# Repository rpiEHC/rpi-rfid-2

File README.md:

# RPI RFID

The goal of RPI RFID is to design, build and test an RPI id card (HID Proxcard II) reader.

## Getting Started

After cloning the repo, execute the following commands to get all the libraries we use for the project.

`git submodule init` 
`git submodule update`

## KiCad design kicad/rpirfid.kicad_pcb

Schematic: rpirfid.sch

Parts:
1K1: R; R_1210
ACT1: LED; LED-1206
C1, C2, C3: 1uF; C_1206
C4, C9, C10, C11: 100nF; C_1206
C5, C6, C7: 10nF; C_1206
C8, C12: 1nF; C_1206
Crystal1: 32.768kHz; Crystal_Round_Horizontal_2mm
D1, D2, D3, D4: LED; LED-1206
IC1: 4050; HEX4045
P1: USB_A
P2: POWER; AK300-2
P3: AVR_PRG_SPI; AK300-2
P4: BATTERY INPUT; AK300-2
R1, R2: 22; R_1206
R3: 10k; R_1206
R4, R7: 470; R_1206
R5, R6: 1k; R_1206
R8: R; R_1206
SW1: SW_PUSH; SW_PUSH_SMALL
U1: ATMEGA32U4-A; TQFP_44
U2: SD_Card_Revised; DIP-8_W7.62mm
U3: EM4095; SOIC-16_3.9x9.9mm_Pitch1.27mm
U4: LM7805; PINHEAD1-3
U5: LD1117S33CTR; PINHEAD1-3
U6: ds1307; DIP-8_W7.62mm
X1: CRYSTAL_SMD; Crystal_Round_Vertical_2mm

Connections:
/3.3V: U2.4, U5.2
/ANT: C8.2, R8.1
/AVR_MISO: P3.1, U1.11, U2.7
/AVR_MOSI: IC1.5, U1.10
/AVR_RESET: R3.1, SW1.2, U1.13
/AVR_SCLK: IC1.3, IC1.9, U1.9
/CDV: C8.1, C12.2, U3.8
/CardDetect: U1.31
/CardSelect: IC1.7, U1.12
/RES_LED: R7.2, U1.29
/RFID_CLK: U1.20, U3.2
/RFID_DATA: U1.21, U3.13
/RFID_EN: U1.25, U3.14
/RFID_MOD: U1.37, U3.12
/RXLED: D1.1, U1.8
/SCL: U1.18, U6.6
/SDA: U1.19, U6.5
/TXLED: D3.1, U1.22
/USB_VBUS: P1.1, U1.2, U1.7
/VBATT: P4.2, U4.1 (VI), U5.3
GND: C1.2, C2.2, C3.1, C5.1, C6.1, C7.1, C12.1, D2.1, D4.1, IC1.11, IC1.14, P1.4, P2.2, P4.1, SW1.1, U1.5, U1.15, U1.23, U1.35, U1.43, U2.6, U3.1, U3.5, U4.2 (GND), U5.1, U6.4
unnamed: 1K1.1, IC1.6, U2.2
unnamed: 1K1.2, ACT1.1
unnamed: ACT1.2, IC1.10
unnamed: C2.1, U1.6
unnamed: C3.2, U1.42
unnamed: C4.1, U3.9
unnamed: C4.2, U3.10
unnamed: C5.2, U3.15
unnamed: C6.2, U3.11
unnamed: C7.2, U3.16
unnamed: C9.1, C10.1, C11.1, U3.6
unnamed: C9.2, C10.2, C11.2
unnamed: Crystal1.1, U6.1
unnamed: Crystal1.2, U6.2
unnamed: D1.2, R5.2
unnamed: D2.2, R4.1
unnamed: D3.2, R6.2
unnamed: D4.2, R7.1
unnamed: IC1.2, U2.5
unnamed: IC1.4, U2.3
unnamed: P1.2, R2.2
unnamed: P1.3, R1.2
unnamed: R1.1, U1.4
unnamed: R2.1, U1.3
unnamed: R8.2, U3.3
unnamed: U1.16, X1.2
unnamed: U1.17, X1.1
VCC: C1.1, IC1.1, P2.1, P3.2, R3.2, R4.2, R5.1, R6.1, U1.14, U1.24, U1.34, U1.44, U3.7, U6.8
VSS: IC1.8

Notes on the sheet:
Real Time Clock
AVR Programmer
Transceiver/Antenna Circuit
USB INPUT
POWER LED
Response LED
TX & RX LED
BATTERY POWER
5V REG
3V REG

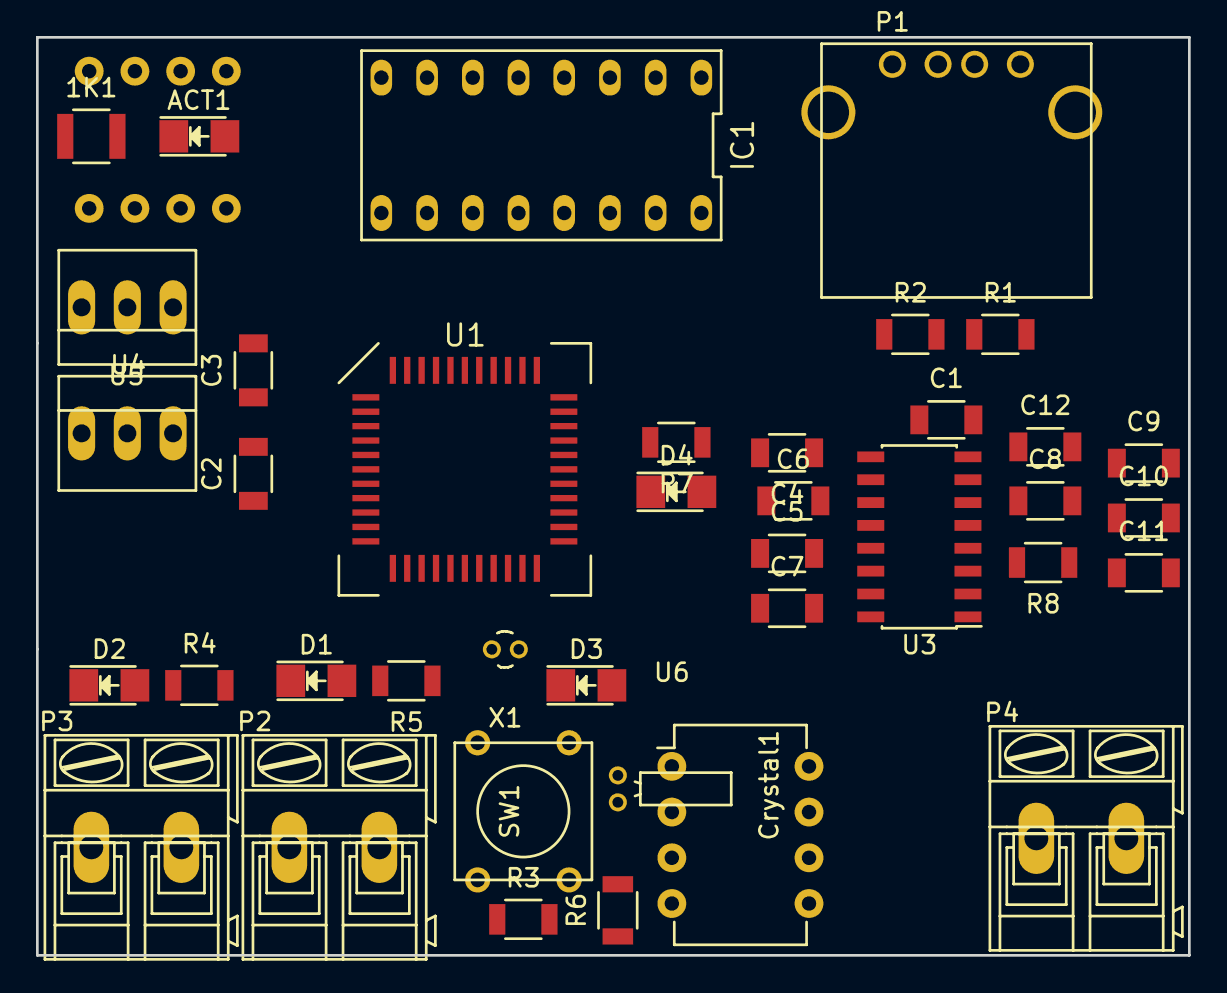
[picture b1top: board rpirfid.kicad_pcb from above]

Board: 2 copper layers, 64.0 x 51.0 mm, 40 parts (1 on the bottom side), 48 nets, no tracks yet.

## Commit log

2015-09-05 initial- old eagle files
2015-09-29 added legacy files
2015-09-29 removed not "up to date" legacy eagle files
2015-10-16 Datasheets
    Datasheets for ICs in the legacy circuit
2015-10-16 More PDFs
    PDFs of the legacy board and schematic
2015-10-16 Even more PDFs and schematics & boards
    Fixed the pdf of the legacy circuit schematic
    Added reference files to the Adafruit microsdcard breakoutboard
2015-10-20 Fixed sd card eagle reference files
    Old files had some weird html stuff in it, replaced with files without
2015-10-21 initial board w/ microcontroller, programmer and usb port (in schematic)
2015-10-21 added microcontroller to datasheets directory
2015-10-30 Custom Library
    Added Part
2015-10-30 Added new component library
2015-10-30 Updated Leglamp library
    Added SD Card to library
2015-10-30 Added real time clock
2015-10-30 Revert "Added real time clock"
    This reverts commit 6b6fc6739ad60bcd637f11be7c206d4bd97eeb06.
2015-11-06 SD_Card added
2015-11-14 SD Card
    Added a Kicad circuit for the SD Card and added another schematic for
    the SD Card in the leglamp library
2015-11-14 Real time clock stuff
2015-11-20 antenna pcb
2015-11-20 added voltage regulator and antenna to schematic
2015-11-20 SD Card
    Added SD Card to the SD Card folder
2015-11-20 Removed the SD_Card circuit from the SD_Card folder
2015-11-20 em4095 module
2015-11-20 Trying to add in SD Card & SD Card Datasheet
2015-11-21 SD Card added to the main file
2015-11-21 Slight update with GND
2015-11-21 Fixed Labels and Connected SD Card to Microcontroller
2015-11-21 Fully connected SD Card and labels
2015-11-21 PCB was started
2015-12-03 created last footprint schematics
2015-12-04 added hex buffer
2015-12-05 corrected name of hex buffer
2015-12-05 SO16 component
2015-12-05 small outline 16
2015-12-05 dip8 comp
2015-12-05 new stuff
2015-12-11 added git submodule for kicad library
2015-12-11 ignore the added submodule
2015-12-11 added kicad library
2015-12-11 all but sd card associated
2015-12-12 PCB layout
2015-12-20 Routing
